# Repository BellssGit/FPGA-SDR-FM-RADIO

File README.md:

# FPGA-SDR-FM-RADIO
FPGA based FM radio with traditional IF architecture and digital IQ demodulation

[more detail (chinese only)](https://www.emoe.xyz/fpga_based_sdr_fm_radio/)

[demo video](https://www.bilibili.com/video/BV1SVxYeYEim/)

credit: https://github.com/alberto-grl/1bitSDR

Note； the PCB project name "R820T_With_LCMXO2" has nothing with R820T frontend IC, it was a thing when I start this PCB, but removed after few revisions.

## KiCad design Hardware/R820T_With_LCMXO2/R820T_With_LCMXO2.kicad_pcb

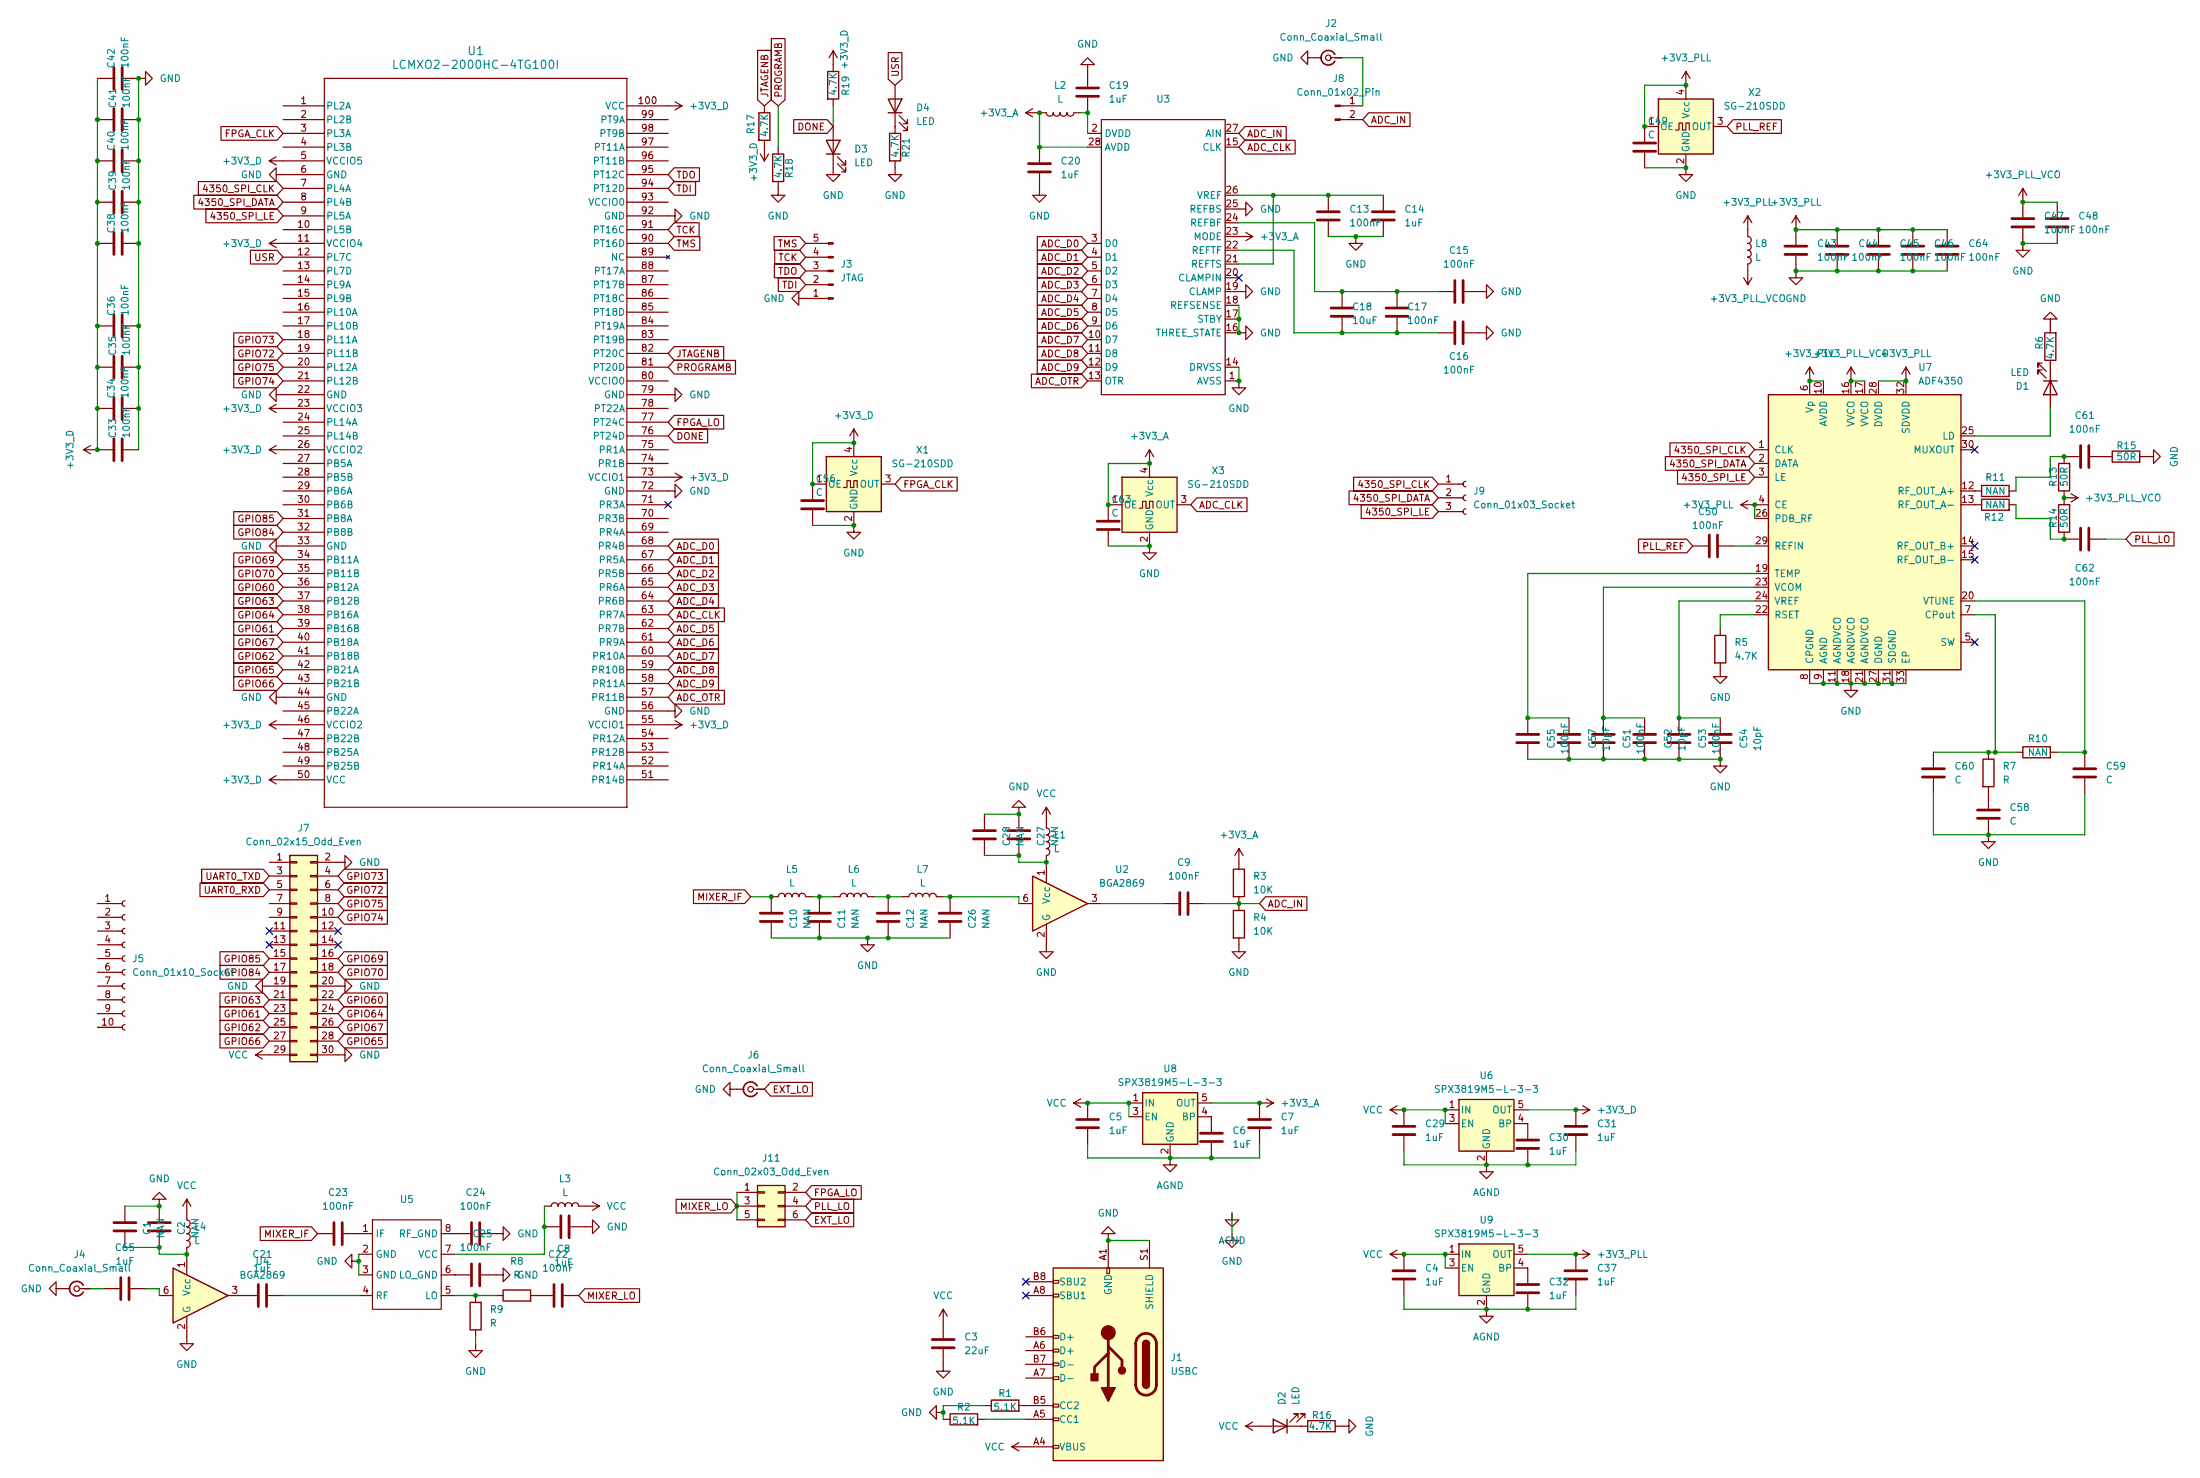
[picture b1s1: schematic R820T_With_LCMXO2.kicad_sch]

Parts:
C1, C2, C10, C11, C12, C26, C27, C28: NAN; C_0603_1608Metric
C3: 22uF; C_0805_2012Metric
C4, C5, C6, C7, C8, C14, C19, C20, C21, C29, C30, C31, C32, C37, C65: 1uF; C_0603_1608Metric
C9, C13, C15, C16, C17, C22, C23, C24, C25, C33, C34, C35, C36, C38, C39, C40, C41, C42, C43, C44, C45, C46, C47, C48, C50, C51, C53, C55, C61, C62, C64: 100nF; C_0603_1608Metric
C18: 10uF; C_0603_1608Metric
C49, C56, C58, C59, C60, C63: C; C_0603_1608Metric
C52, C54, C57: 10pF; C_0603_1608Metric
D1, D2, D3, D4: LED; LED_0603_1608Metric
J1: USBC; USB_C_Receptacle_G-Switch_GT-USB-7010ASV
J2, J4, J6: Conn_Coaxial_Small; SMA_Samtec_SMA-J-P-H-ST-EM1_EdgeMount_FIX_edge
J3: JTAG; PinSocket_1x05_P2.54mm_Vertical
J5: Conn_01x10_Socket; PinSocket_1x10_P2.54mm_Vertical
J7: Conn_02x15_Odd_Even; PinSocket_2x15_P2.54mm_Vertical
J8: Conn_01x02_Pin; PinHeader_1x02_P2.54mm_Vertical
J9: Conn_01x03_Socket; PinSocket_1x03_P2.54mm_Vertical
J11: Conn_02x03_Odd_Even; PinHeader_2x03_P2.54mm_Vertical
L1, L2, L3, L4, L8: L; L_0805_2012Metric
L5, L6, L7: L; L_0603_1608Metric
R1, R2: 5.1K; R_0603_1608Metric
R3, R4: 10K; R_0603_1608Metric
R5, R6, R16, R17, R18, R19, R21: 4.7K; R_0603_1608Metric
R7, R8, R9: R; R_0603_1608Metric
R10, R11, R12: NAN; R_0603_1608Metric
R13, R14, R15: 50R; R_0603_1608Metric
U1: LCMXO2-2000HC-4TG100I; TQFP-100_14x14mm_P0.5mm
U2, U4: BGA2869; SOT-363_SC-70-6
U3: SSOP-28_5.3x10.2mm_P0.65mm
U5: SO-8_3.9x4.9mm_P1.27mm
U6, U8, U9: SPX3819M5-L-3-3; SOT-23-5
U7: ADF4350; LFCSP-32-1EP_5x5mm_P0.5mm_EP3.25x3.25mm
X1, X2, X3: SG-210SDD; Oscillator_SMD_Abracon_ASE-4Pin_3.2x2.5mm

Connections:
4350_SPI_CLK: J9.1, U1.7 (PL4A), U7.1 (CLK)
4350_SPI_DATA: J9.2, U1.8 (PL4B), U7.2 (DATA)
4350_SPI_LE: J9.3, U1.9 (PL5A), U7.3 (LE)
+3V3_A: C7.1, C20.2, C63.1, L2.2, R3.1, U3.23 (MODE), U3.28 (AVDD), U8.5 (OUT), X3.1 (OE), X3.4 (Vcc)
+3V3_D: C31.1, C33.1, C34.1, C35.1, C36.1, C38.1, C39.1, C40.1, C41.1, C42.1, C56.1, R17.2, R19.1, U1.5 (VCCIO5), U1.11 (VCCIO4), U1.23 (VCCIO3), U1.26 (VCCIO2), U1.46 (VCCIO2), U1.50 (VCC), U1.55 (VCCIO1), U1.73 (VCCIO1), U1.100 (VCC), U6.5 (OUT), X1.1 (OE), X1.4 (Vcc)
+3V3_PLL: C37.1, C43.1, C44.1, C45.1, C46.1, C49.1, C64.1, L8.1, U7.4 (CE), U7.6 (Vp), U7.10 (AVDD), U7.26 (PDB_RF), U7.28 (DVDD), U7.32 (SDVDD), U9.5 (OUT), X2.1 (OE), X2.4 (Vcc)
+3V3_PLL_VCO: C47.1, C48.1, L8.2, R13.1, R14.2, U7.16 (VVCO), U7.17 (VVCO)
ADC_CLK: U1.63 (PR7A), U3.15 (CLK), X3.3 (OUT)
ADC_D0: U1.68 (PR4B), U3.3 (D0)
ADC_D1: U1.67 (PR5A), U3.4 (D1)
ADC_D2: U1.66 (PR5B), U3.5 (D2)
ADC_D3: U1.65 (PR6A), U3.6 (D3)
ADC_D4: U1.64 (PR6B), U3.7 (D4)
ADC_D5: U1.62 (PR7B), U3.8 (D5)
ADC_D6: U1.61 (PR9A), U3.9 (D6)
ADC_D7: U1.60 (PR10A), U3.10 (D7)
ADC_D8: U1.59 (PR10B), U3.11 (D8)
ADC_D9: U1.58 (PR11A), U3.12 (D9)
ADC_IN: C9.2, J8.2, R3.2, R4.1, U3.27 (AIN)
ADC_OTR: U1.57 (PR11B), U3.13 (OTR)
AGND: C1.2, C2.2, C3.2, C4.2, C5.2, C6.2, C7.2, C8.2, C10.1, C11.1, C12.1, C13.2, C14.2, C15.2, C16.2, C19.2, C20.1, C24.2, C25.2, C26.1, C27.2, C28.2, C29.2, C30.2, C31.2, C32.2, C33.2, C34.2, C35.2, C36.2, C37.2, C38.2, C39.2, C40.2, C41.2, C42.2, C43.2, C44.2, C45.2, C46.2, C47.2, C48.2, C49.2, C51.1, C52.1, C53.1, C54.1, C55.1, C56.2, C57.1, C58.2, C59.2, C60.2, C63.2, C64.2, D3.1 (K), J1.A1 (GND), J1.A12 (GND), J1.B1 (GND), J1.B12 (GND), J1.S1 (SHIELD), J2.2 (Ext), J3.1, J4.2 (Ext), J6.2 (Ext), J7.2, J7.19, J7.20, J7.30, R1.1, R2.1, R4.2, R5.2, R6.2, R9.1, R15.2, R16.2, R18.2, R21.2, U1.6 (GND), U1.22 (GND), U1.33 (GND), U1.44 (GND), U1.56 (GND), U1.72 (GND), U1.79 (GND), U1.92 (GND), U2.2 (G), U2.4 (G), U2.5 (G), U3.1 (AVSS), U3.14 (DRVSS), U3.16 (THREE_STATE), U3.17 (STBY), U3.18 (REFSENSE), U3.19 (CLAMP), U3.25 (REFBS), U4.2 (G), U4.4 (G), U4.5 (G), U5.2 (GND), U5.3 (GND), U6.2 (GND), U7.8 (CPGND), U7.9 (AGND), U7.11 (AGNDVCO), U7.18 (AGNDVCO), U7.21 (AGNDVCO), U7.27 (DGND), U7.31 (SDGND), U7.33 (EP), U8.2 (GND), U9.2 (GND), X1.2 (GND), X2.2 (GND), X3.2 (GND)
DONE: D3.2 (A), R19.2, U1.76 (PT24D)
EXT_LO: J6.1 (In), J11.6
FPGA_CLK: U1.3 (PL3A), X1.3 (OUT)
FPGA_LO: J11.2, U1.77 (PT24C)
GPIO60: J7.22, U1.36 (PB12A)
GPIO61: J7.23, U1.39 (PB16B)
GPIO62: J7.25, U1.41 (PB18B)
GPIO63: J7.21, U1.37 (PB12B)
GPIO64: J7.24, U1.38 (PB16A)
GPIO65: J7.28, U1.42 (PB21A)
GPIO66: J7.27, U1.43 (PB21B)
GPIO67: J7.26, U1.40 (PB18A)
GPIO69: J7.16, U1.34 (PB11A)
GPIO70: J7.18, U1.35 (PB11B)
GPIO72: J7.6, U1.19 (PL11B)
GPIO73: J7.4, U1.18 (PL11A)
GPIO74: J7.10, U1.21 (PL12B)
GPIO75: J7.8, U1.20 (PL12A)
GPIO84: J7.17, U1.32 (PB8B)
GPIO85: J7.15, U1.31 (PB8A)
JTAGENB: R17.1, U1.82 (PT20C)
MIXER_IF: C10.2, C23.1, L5.1
MIXER_LO: C22.2, J11.1, J11.3, J11.5
unnamed: C9.1, U2.3
unnamed: C11.2, L5.2, L6.1
unnamed: C12.2, L6.2, L7.1
unnamed: C21.1, U4.3
unnamed: C22.1, R8.2
unnamed: C26.2, L7.2, U2.6
unnamed: C58.1, R7.2
unnamed: C61.1, R11.2, R13.2
unnamed: C61.2, R15.1
unnamed: C62.1, R12.2, R14.1
unnamed: C65.2, U4.6
unnamed: D1.2 (A), U7.25 (LD)
unnamed: D1.1 (K), R6.1
unnamed: D2.1 (K), R16.1
unnamed: D4.1 (K), R21.1
unnamed: J1.A5 (CC1), R2.2
unnamed: J1.B5 (CC2), R1.2
unnamed: J2.1 (In), J8.1
unnamed: C65.1, J4.1 (In)
unnamed: C27.1, C28.1, L1.2, U2.1 (Vcc)
unnamed: C19.1, L2.1, U3.2 (DVDD)
unnamed: C15.1, C17.2, C18.2, U3.24 (REFBF)
unnamed: C16.1, C17.1, C18.1, U3.22 (REFTF)
unnamed: C13.1, C14.1, U3.21 (REFTS), U3.26 (VREF)
unnamed: C1.1, C2.1, L4.2, U4.1 (Vcc)
unnamed: C23.2, U5.1 (IF)
unnamed: R8.1, R9.2, U5.5 (LO)
unnamed: C25.1, U5.6 (LO_GND)
unnamed: C21.2, U5.4 (RF)
unnamed: C24.1, U5.8 (RF_GND)
unnamed: C8.1, L3.1, U5.7 (VCC)
unnamed: C30.1, U6.4 (BP)
unnamed: C60.1, R7.1, R10.1, U7.7 (CPout)
unnamed: C50.2, U7.29 (REFIN)
unnamed: R11.1, U7.12 (RF_OUT_A+)
unnamed: R12.1, U7.13 (RF_OUT_A-)
unnamed: R5.1, U7.22 (RSET)
unnamed: C55.2, C57.2, U7.19 (TEMP)
unnamed: C51.2, C52.2, U7.23 (VCOM)
unnamed: C53.2, C54.2, U7.24 (VREF)
unnamed: C59.1, R10.2, U7.20 (VTUNE)
unnamed: C6.1, U8.4 (BP)
unnamed: C32.1, U9.4 (BP)
PLL_LO: C62.2, J11.4
PLL_REF: C50.1, X2.3 (OUT)
PROGRAMB: R18.1, U1.81 (PT20D)
TCK: J3.4, U1.91 (PT16C)
TDI: J3.2, U1.94 (PT12D)
TDO: J3.3, U1.95 (PT12C)
TMS: J3.5, U1.90 (PT16D)
UART0_RXD: J7.5
UART0_TXD: J7.3
USR: D4.2 (A), U1.12 (PL7C)
VCC: C3.1, C4.1, C5.1, C29.1, D2.2 (A), J1.A4 (VBUS), J1.A9 (VBUS), J1.B4 (VBUS), J1.B9 (VBUS), J7.29, L1.1, L3.2, L4.1, U6.1 (IN), U6.3 (EN), U8.1 (IN), U8.3 (EN), U9.1 (IN), U9.3 (EN)

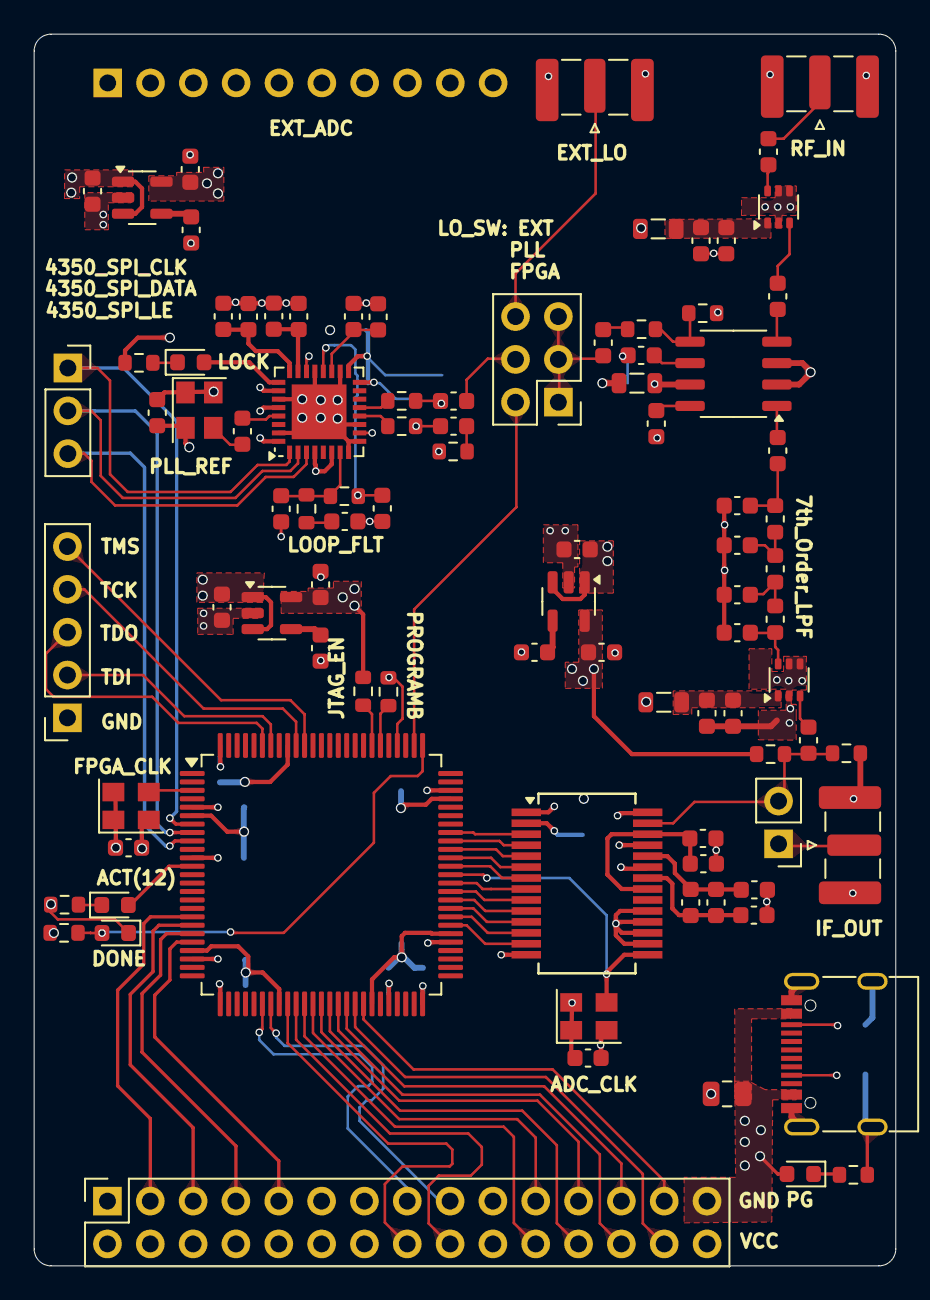
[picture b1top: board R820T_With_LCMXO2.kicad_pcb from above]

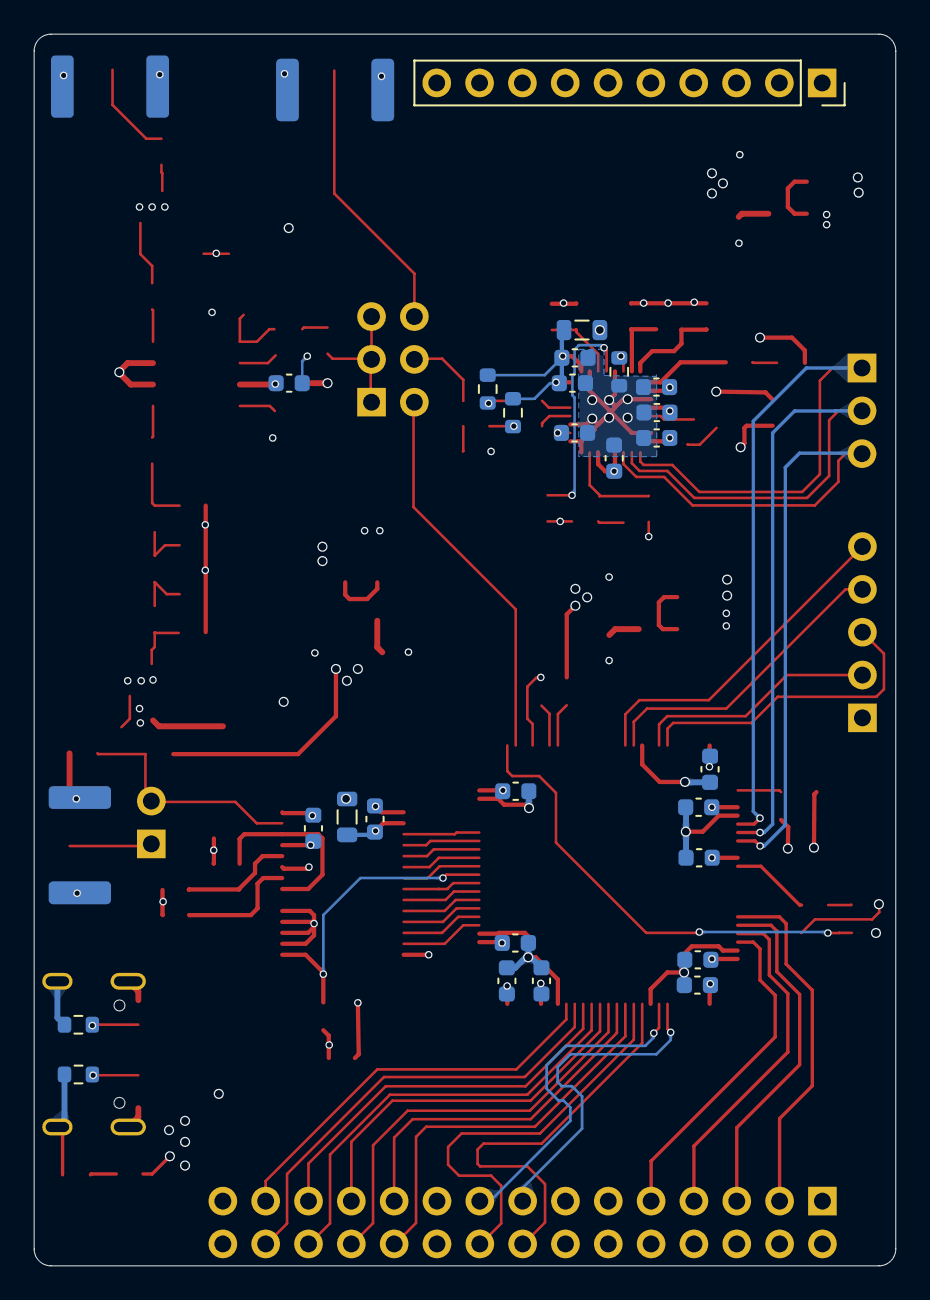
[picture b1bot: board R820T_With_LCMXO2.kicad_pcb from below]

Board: 4 copper layers, 51.1 x 73.0 mm, 119 parts (27 on the bottom side), 96 nets.

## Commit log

2024-10-01 Add Hardware and Firmware
